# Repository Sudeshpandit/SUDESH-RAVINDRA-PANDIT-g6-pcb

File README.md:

# USB-TO-EtherCAT-Adapter-Board

A compact USB-to-EtherCAT adapter board that allows a USB host system to communicate with an EtherCAT network. An STM32 microcontroller handles the USB side and exchanges data with a LAN9252 EtherCAT slave controller, which manages the fieldbus protocol and drives two RJ45 ports for daisy-chain operation. The board is bus-powered from USB and designed in KiCad for industrial automation, embedded systems, and real-time networking use.

---

## Key Goals

**1. Reliable protocol bridging**
Provide a stable conversion path between USB and EtherCAT so a standard host machine can participate in a deterministic industrial network without dedicated fieldbus hardware.

**2. Standards-compliant hardware design**
Follow proper high-speed design practice — controlled differential routing, correct termination, clean power distribution, and stable clocking — so the board meets EtherCAT physical-layer requirements and operates reliably in noisy environments.

**3. Compact and practical integration**
Keep the board bus-powered, self-contained, and small enough to sit inline in an existing network, with edge-mounted connectors, mounting holes, and a debug header for easy deployment and development.

---

## Features

**Communication**
Full signal chain from USB host through the microcontroller to the EtherCAT slave controller, with two RJ45 ports allowing the adapter to be placed anywhere in a daisy-chained network.

**Design quality**
Length-matched differential pairs, proper termination networks, dedicated filtered supply rails, per-pin decoupling, and independent clock sources for the controller and the EtherCAT device.

**Usability**
Single-cable USB power, on-board 3.3 V regulation, status LEDs, reset switch, SWD programming header, and mounting holes for enclosure fitting.

---

## Hardware

| Item | Detail |
|---|---|
| Microcontroller | STM32F411CEUx (ARM Cortex-M4) |
| EtherCAT slave controller | Microchip LAN9252 |
| Configuration memory | 24LC512 I²C EEPROM |
| Network ports | 2x RJ45 (IN / OUT, integrated magnetics) |
| Host interface | USB |
| Power | USB bus powered, AMS1117-3.3 regulator |
| Debug | 4-pin SWD header |
| Design software | KiCad |

---

## Software and Tools Used

| Tool | Purpose |
|---|---|
| **KiCad** | Schematic capture, PCB layout, DRC/ERC |
| **KiCad Symbol & Footprint Editor** | Custom symbols and footprints |
| **KiCad 3D Viewer** | Mechanical and visual verification |
| **Gerber Viewer** | Fabrication output verification |

---

## Outputs / Deliverables

- Schematic (KiCad + PDF export)
- PCB layout (KiCad + PDF export)
- Gerber files (fabrication-ready)
- Drill files
- Bill of Materials (BOM)
- Pick and place file
- 3D render

---

## Applications

- Industrial automation and motion control
- EtherCAT slave/master development and testing
- Embedded systems requiring fieldbus connectivity
- Real-time networking and data acquisition setups

## Author

**Sudesh Pandit**
*(https://www.linkedin.com/in/sudeshpandits/)*

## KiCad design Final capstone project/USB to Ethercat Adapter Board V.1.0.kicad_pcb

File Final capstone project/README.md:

<div align="center" style="border: 2px solid #ccc; padding: 20px; border-radius: 12px; width: 80%; margin: auto; box-shadow: 0 0 10px rgba(0,0,0,0.15);">

  <h1 align="center" style="font-family: Arial; font-weight: 600; margin-top: 15px;">SURE ProEd (formerly SURE Trust) 
      </h1>
<h2 style="color: #2b6cb0; font-family: Arial;">Skill Upgradation for Rural youth Empowerment Trust</h2>
</div>

<hr style="border: 0; border-top: 1px solid #ccc; width: 80%;" />

<div style="padding: 20px; border: 2px solid #ddd; border-radius: 12px; width: 90%; margin: auto; background: #fafafa; font-family: Arial;">

<h2 style = "color:#333;"> Student Details </h2>
<div align = "left" style ="margin: 20px; font-size: 16px;">
    <p><strong>Name:</strong> Sudesh Ravindra Pandit </p>
    <p><strong>Email ID:</strong> sudeshpanditg6pcb@gmail.com </p>
    <p><strong>College Name:</strong> Dhole Patil College Of Engineering ,Pune  </p>
    <p><strong>Branch/Specialization :</strong> Electronics and Telecommunication Engineering </p>
    <p><strong>College ID:</strong> EN22170156 </p>
</div>

<hr style="border: 0; border-top: 1px solid #ccc; width: 80%;" />

<h2 style="color:#333;"> Course Details </h2>
<div align="left" style="margin: 20px; font-size: 16px;">
    <p><strong>Course Opted:</strong> PCB Designing </p>
    <p><strong>Instructor Name:</strong> Monika mam </p>
</div>
<div align="left" style="margin: 20px; font-size: 16px;">
    <p><strong>Duration:</strong> 6 Months </p>

<hr style="border: 0; border-top: 1px solid #ccc; width: 80%;" />

<h2 style="color:#333;"> Trainer Details </h2>
<div align="left" style="margin: 20px; font-size: 16px;">

<p><strong>Trainer Name:</strong> Paramesh Kumar </p>
<p><strong>Trainer Email ID:</strong> parameshkumar432@gmail.com </p>
<p><strong>Trainer Designation:</strong> Hardware Design Engineer </p>

<hr style="border: 0; border-top: 1px solid #ccc; width: 80%;" />

## **Table of Contents**
- [Course Learning](#course-learning-to-be-edited-by-student)
- [Projects Completed](#projects-completed)
- [Project Introduction](#project-introduction)
- [Technologies Used](#technologies-used)
- [Roles and Responsibilities](#roles-and-responsibilities)
- [Project Report](#project-report)
- [Learnings from LST & SST](#learnings-from-lst--sst)
- [Community Services](#community-services)
- [Certificate](#certificate)
- [Acknowledgments](#acknowledgments)

<hr style="border: 0; border-top: 1px solid #ccc; width: 80%;" />

## Overall Learning 

When I started, I barely knew how a PCB actually gets made — the first few days were confusing, and I kept hitting DRC errors without understanding why. Things started clicking as I worked through mistakes instead of just reading about them.

Over the internship I built up through 14 PCB projects, gaining hands-on experience with STM32 microcontrollers, SPI/I2C communication, and industrial protocols like EtherCAT — along the way strengthening my problem-solving (debugging DRC errors and routing conflicts), documentation, and the discipline of verifying a design before calling it done.

My final project, the USB to EtherCAT Adapter Board, brought a lot of that learning together — it needed me to combine what I'd picked up about power supply design, layout planning, and following proper design rules into one board.

Overall, this internship taught me that PCB design isn't something you understand by reading — you actually have to sit with the confusion for a while before it starts making sense.

<h2 style="color:#333;"> Projects Completed </h2>
<div align="left" style="margin: 20px; font-size: 16px;">

<p><strong><a href="#project1">Project 1:</a></strong> USB to EtherCAT Adapter Board V.1.0 </p>

<p><em></em></p>

</div>

<!-- Project 1 -->
<h3 id="project1">Project 1: USB to EtherCAT Adapter Board V.1.0 </h3>
<p>
 This project was completed as part of my internship at SURE Trust, where I designed and developed a 2-layer USB to EtherCAT Adapter Board (V1.0) using KiCad, applying core PCB design concepts taught during the training.
It focused on schematic design around an STM32F411 microcontroller and a LAN9252 EtherCAT slave controller, structured 2-layer routing with proper design-rule compliance, and implementing key features like USB communication, SPI/I2C interfacing, and dual RJ45 EtherCAT ports.
</p>
<p>
  <a href="https://github.com/sure-trust/SUDESH-RAVINDRA-PANDIT-g6-pcb/blob/492f94ba0c24407fa2a5996a74b2673d0c09e90f/Course%20report/SURE%20Trust%20Final%20Project%20%20Report.pdf" target="_blank"><strong>→ View Full Project Report</strong></a>
</p>

<hr style="height:1px; border-top:1px solid #ccc; width:80%;" />

## **References**

- [Wikipedia](https://wikipedia.com)
<!--you can add refrences over here in same syntax as above -->
---

## **Learnings from LST and SST**

<!-- add your experiences over here -->
Alongside the technical PCB work, we had daily Life Skill Training (LST) and Soft Skill Training (SST) sessions, where a different guest speaker was invited almost every day. What stood out to me was who these speakers actually were — professionals holding senior positions at well-known companies — sharing real experience rather than just theory from a textbook.

Honestly, some sessions connected with me more than others depending on the topic, but hearing people who've actually worked at that level talk about how they think, communicate, and handle real workplace situations gave me a different perspective than just focusing on the technical side of the internship. It made me realize that skills like communication, confidence, and how you present yourself matter just as much as technical ability when it comes to actually working in the industry.

## **Community Services**

<!-- add descreption in your own words -->

During my internship period, I participated in multiple community-oriented activities .....<!-- add descreption in your own words -->

### **Activities Involved**
  
 <!-- add the location where you have panted -->
- **Tree Plantation Drive** – Participated by planting trees and contributing to environmental improvement.

  <!-- add the location where you helped -->
- **Helping Elder Citizens** – Assisted two elderly individuals with simple daily tasks and provided support where needed. 

<!-- you can write impacts according to your experience in your words-->

### **Impact / Contribution**

<!-- add the location where you given -->
Tree Plantation Drive – Participated by planting trees and contributing to environmental improvement.
Helping Elder Citizens – Assisted two elderly individuals with simple daily tasks and provided support where needed.
These activities, alongside the core PCB design work, strengthened my sense of social responsibility and community engagement, reflecting SURE Trust's focus on holistic development beyond just technical skills.
### **Photos**

<!-- add your photos below -->
<!-- change url below with your image urls (inside  src='')-->

- These are just placeholder (sample) images <!-- remove this line -->

<div align="center">

</div>

---

## **Certificate**

The internship certificate serves as an official acknowledgment of the successful completion of my training period. It will be issued by the organization upon fulfilling all required tasks and meeting the performance expectations of the program. The certificate validates the skills, experience, and contributions made during the internship.

<!-- add your certificate image url below (inside src='')-->

---

## **Acknowledgments**

<!-- you can add Acknowledgments over here in same syntax as below . eg trainer name , company name , role etc -->

- [Prof. Radhakumari Challa](https://www.linkedin.com/in/prof-radhakumari-challa-a3850219b) , Executive Director and Founder - [SURE Trust](https://www.suretrustforruralyouth.com/)

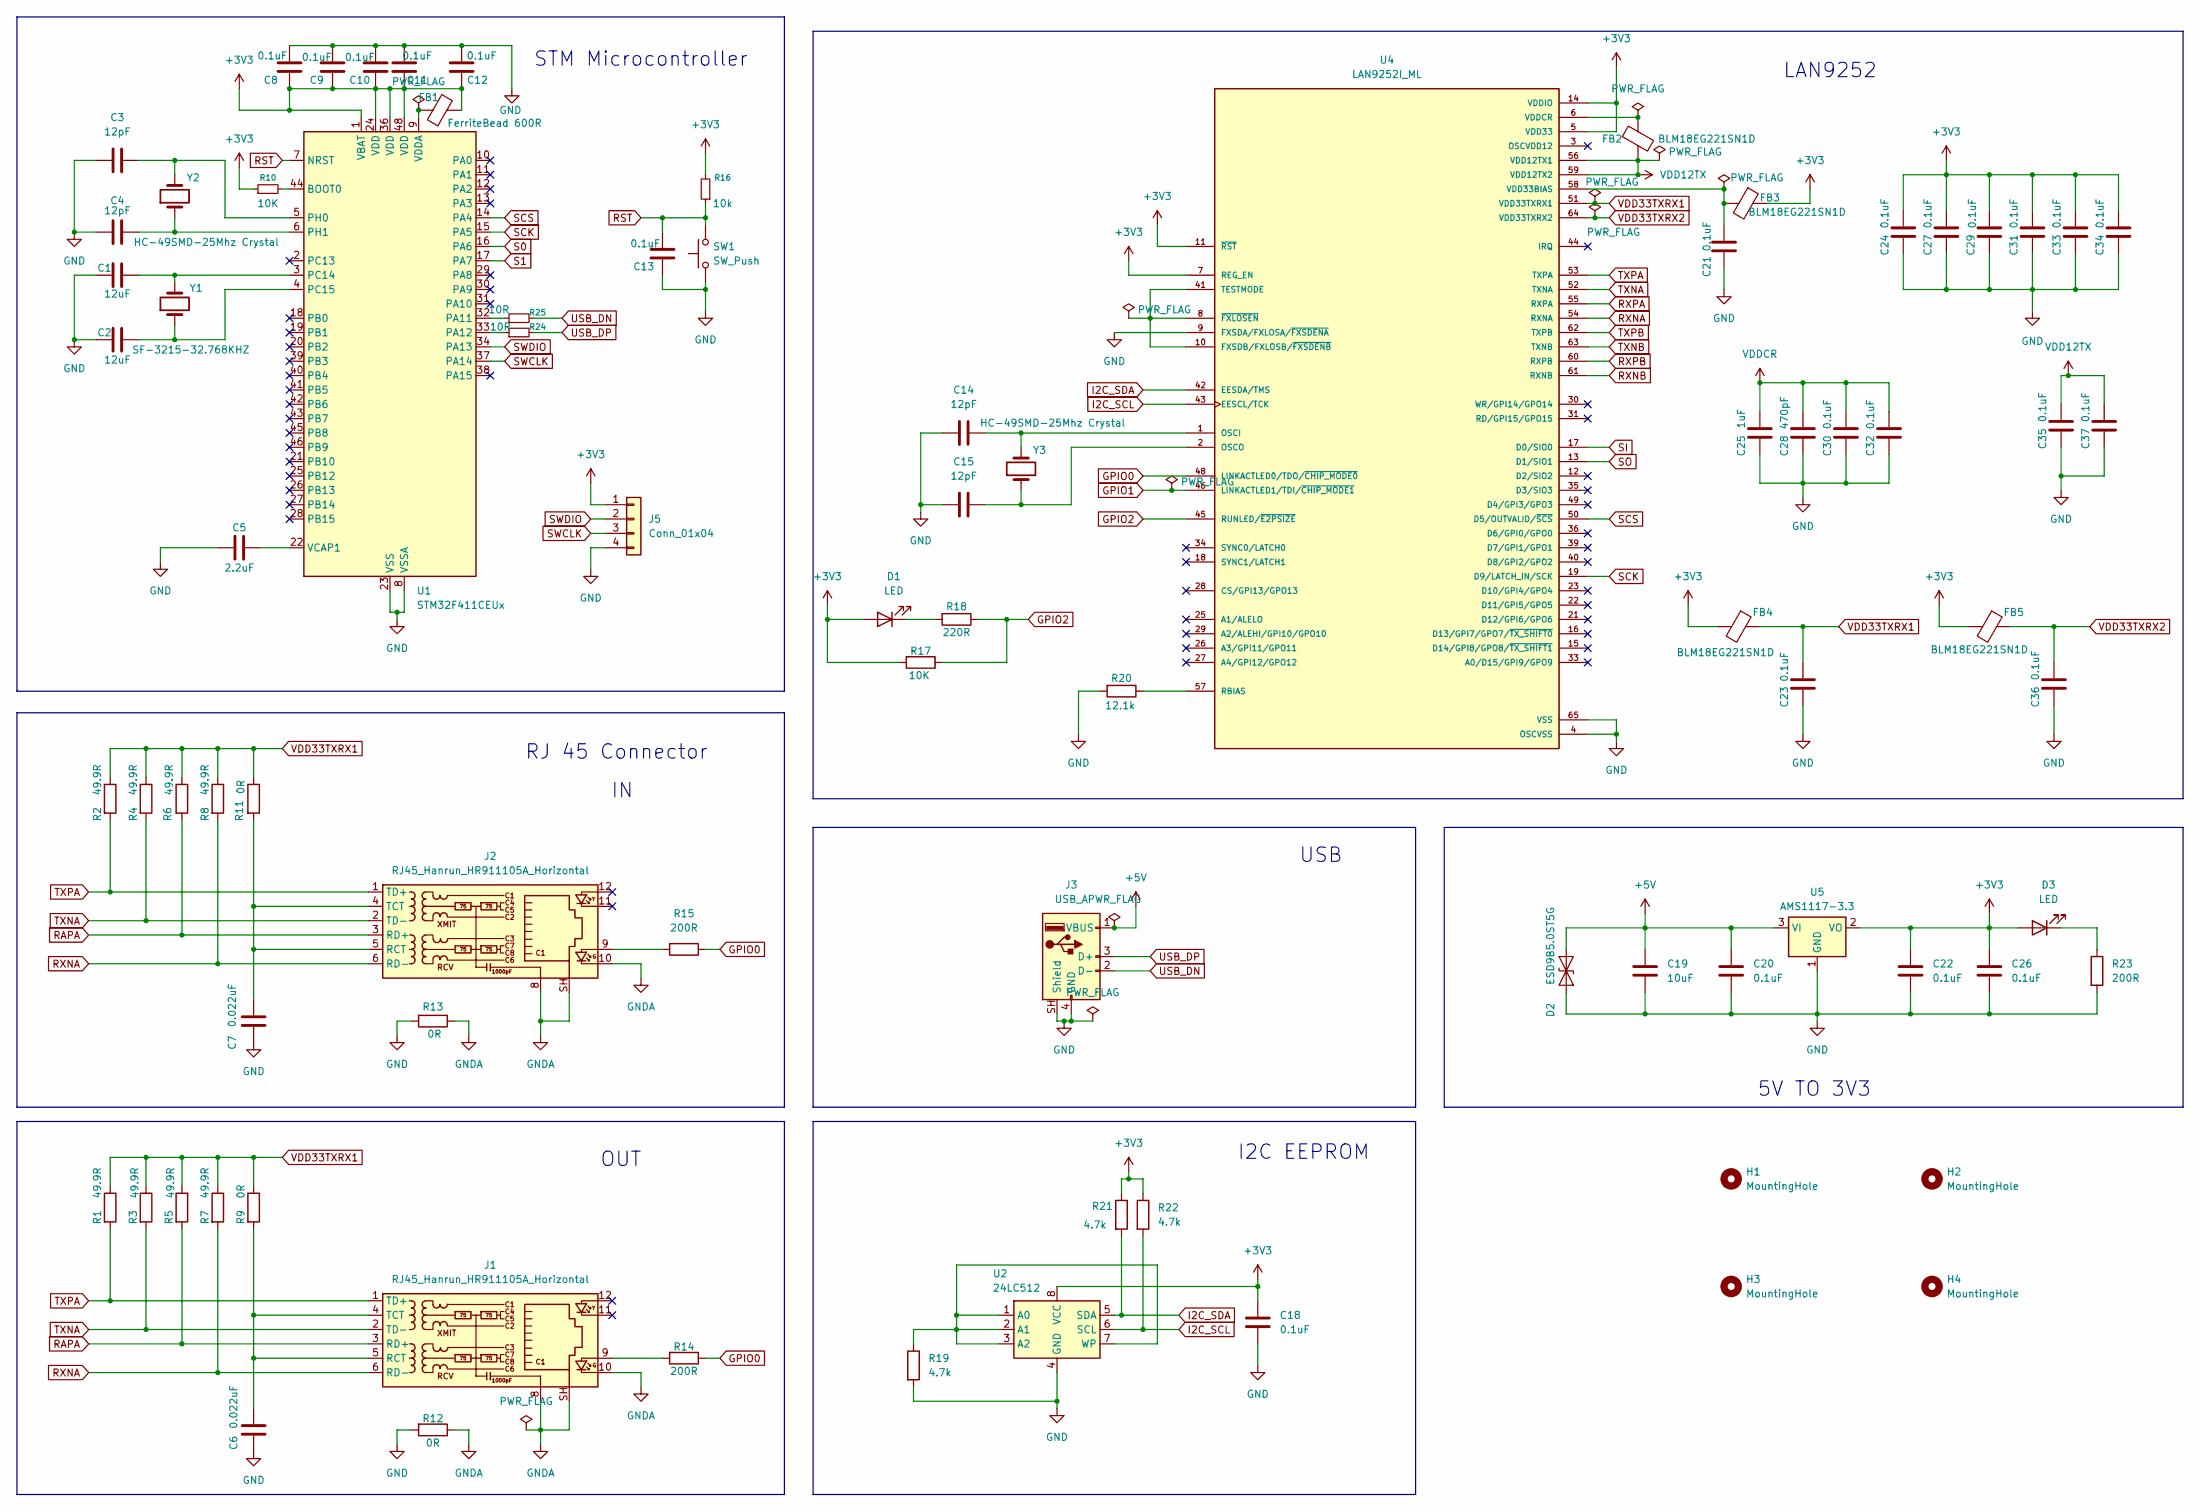
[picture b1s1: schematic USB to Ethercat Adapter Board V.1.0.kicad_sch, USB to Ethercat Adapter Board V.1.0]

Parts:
C1, C2: 12uF; C_0603_1608Metric
C3, C4, C14, C15: 12pF; C_0603_1608Metric
C5: 2.2uF; C_0805_2012Metric
C6, C7: 0.022uF; C_0603_1608Metric
C8, C9, C10, C11, C12, C13, C18, C20, C21, C22, C23, C24, C27, C29, C30, C31, C32, C33, C34, C35, C36, C37: 0.1uF; C_0603_1608Metric
C19: 10uF; C_0805_2012Metric
C25: 1uF; C_0603_1608Metric
C26: 0.1uF; C_0805_2012Metric
C28: 470pF; C_0603_1608Metric
D1, D3: LED; LED_0603_1608Metric
D2: ESD9B5.0ST5G; C_0805_2012Metric
FB1: FerriteBead 600R; L_0603_1608Metric
FB2, FB3, FB4, FB5: BLM18EG221SN1D; L_0603_1608Metric
H1, H2, H3, H4: MountingHole; MountingHole_3.2mm_M3
J1, J2: RJ45_Hanrun_HR911105A_Horizontal
J3: USB_A; USB_A_CNCTech_1001-011-01101_Horizontal
J5: Conn_01x04; PinHeader_1x04_P2.54mm_Vertical
R1, R2, R3, R4, R5, R6, R7, R8: 49.9R; R_0603_1608Metric
R9, R11, R12, R13: 0R; R_0603_1608Metric
R10, R17: 10K; R_0603_1608Metric
R14, R15, R23: 200R; R_0603_1608Metric
R16: 10k; R_0603_1608Metric
R18: 220R; R_0603_1608Metric
R19, R21, R22: 4.7k; R_0603_1608Metric
R20: 12.1k; R_0603_1608Metric
R24, R25: 10R; R_0603_1608Metric
SW1: SW_Push; SW_SPST_B3U-1000P
U1: STM32F411CEUx; QFN-48-1EP_7x7mm_P0.5mm_EP5.6x5.6mm
U2: 24LC512; TSSOP-8_3x3mm_P0.65mm
U4: LAN9252I_ML; QFN50P900X900X100-65N-; PARTREV DS00001909B
U5: AMS1117-3.3; SOT-223-3_TabPin2
Y1: SF-3215-32.768KHZ; Crystal_SMD_3215-2Pin_3.2x1.5mm
Y2, Y3: HC-49SMD-25Mhz Crystal; Crystal_SMD_HC49-SD

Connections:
+3V3: C8.1, C9.1, C10.1, C11.1, C12.1, C18.2, C22.2, C24.2, C26.2, C27.2, C29.2, C31.2, C33.2, C34.2, D1.2 (A), D3.2 (A), FB1.2, FB3.1, FB4.2, FB5.2, J5.1, R10.1, R16.2, R17.2, R21.1, R22.1, U1.1 (VBAT), U1.24 (VDD), U1.36 (VDD), U1.48 (VDD), U2.8 (VCC), U4.5 (VDD33), U4.7 (REG_EN), U4.11 (~RST), U4.14 (VDDIO), U4.20 (VDDIO), U4.32 (VDDIO), U4.37 (VDDIO), U4.47 (VDDIO), U5.2 (VO)
+5V: C19.2, C20.2, D2.2 (A2), J3.1 (VBUS), U5.3 (VI)
GND: C1.1, C2.1, C3.1, C4.1, C5.1, C6.2, C7.2, C8.2, C9.2, C10.2, C11.2, C12.2, C13.1, C14.1, C15.1, C18.1, C19.1, C20.1, C21.1, C22.1, C23.1, C24.1, C25.1, C26.1, C27.1, C28.1, C29.1, C30.1, C31.1, C32.1, C33.1, C34.1, C35.1, C36.1, C37.1, D2.1 (A1), J3.4 (GND), J3.SH (Shield), J5.4, R12.2, R13.2, R19.2, R20.2, R23.2, SW1.1, U1.8 (VSSA), U1.23 (VSS), U1.35 (VSS), U1.47 (VSS), U1.49 (VSS), U2.4 (GND), U4.4 (OSCVSS), U4.9 (FXSDA/FXLOSA/~FXSDENA), U4.65 (VSS), U5.1 (GND)
GNDA: J1.8, J1.10, J1.SH, J2.8, J2.10, J2.SH, R12.1, R13.1
GPIO0: R14.1, R15.1, U4.48 (LINKACTLED0/TDO/~CHIP_MODE0)
GPIO1: U4.46 (LINKACTLED1/TDI/~CHIP_MODE1)
GPIO2: R17.1, R18.1, U4.45 (RUNLED/~E2PSIZE)
I2C_SCL: R22.2, U2.6 (SCL), U4.43 (EESCL/TCK)
I2C_SDA: R21.2, U2.5 (SDA), U4.42 (EESDA/TMS)
unnamed: D1.1 (K), R18.2
unnamed: D3.1 (K), R23.1
unnamed: J1.9, R14.2
unnamed: C6.1, J1.4 (TCT), J1.5 (RCT), R9.2
unnamed: J2.9, R15.2
unnamed: C7.1, J2.4 (TCT), J2.5 (RCT), R11.2
unnamed: R10.2, U1.44 (BOOT0)
unnamed: R25.1, U1.32 (PA11)
unnamed: R24.1, U1.33 (PA12)
unnamed: C1.2, U1.3 (PC14), Y1.2
unnamed: C2.2, U1.4 (PC15), Y1.1
unnamed: C3.2, U1.5 (PH0), Y2.2
unnamed: C4.2, U1.6 (PH1), Y2.1
unnamed: C5.2, U1.22 (VCAP1)
unnamed: FB1.1, U1.9 (VDDA)
unnamed: R19.1, U2.1 (A0), U2.2 (A1), U2.3 (A2), U2.7 (WP)
unnamed: U4.8 (~FXLOSEN), U4.10 (FXSDB/FXLOSB/~FXSDENB), U4.41 (TESTMODE)
unnamed: C14.2, U4.1 (OSCI), Y3.2
unnamed: C15.2, U4.2 (OSCO), Y3.1
unnamed: R20.1, U4.57 (RBIAS)
unnamed: C21.2, FB3.2, U4.58 (VDD33BIAS)
RAPA: J1.3 (RD+), J2.3 (RD+), R5.2, R6.2
RST: C13.2, R16.1, SW1.2, U1.7 (NRST)
RXNA: J1.6 (RD-), J2.6 (RD-), R7.2, R8.2, U4.54 (RXNA)
RXNB: U4.61 (RXNB)
RXPA: U4.55 (RXPA)
RXPB: U4.60 (RXPB)
S0: U1.16 (PA6)
S1: U1.17 (PA7)
SCK: U1.15 (PA5), U4.19 (D9/LATCH_IN/SCK)
SCS: U1.14 (PA4), U4.50 (D5/OUTVALID/~SCS)
SI: U4.17 (D0/SIO0)
SO: U4.13 (D1/SIO1)
SWCLK: J5.3, U1.37 (PA14)
SWDIO: J5.2, U1.34 (PA13)
TXNA: J1.2 (TD-), J2.2 (TD-), R3.2, R4.2, U4.52 (TXNA)
TXNB: U4.63 (TXNB)
TXPA: J1.1 (TD+), J2.1 (TD+), R1.2, R2.2, U4.53 (TXPA)
TXPB: U4.62 (TXPB)
USB_DN: J3.2 (D-), R25.2
USB_DP: J3.3 (D+), R24.2
VDD12TX: C35.2, C37.2, FB2.2, U4.56 (VDD12TX1), U4.59 (VDD12TX2)
VDD33TXRX1: C23.2, FB4.1, R1.1, R2.1, R3.1, R4.1, R5.1, R6.1, R7.1, R8.1, R9.1, R11.1, U4.51 (VDD33TXRX1)
VDD33TXRX2: C36.2, FB5.1, U4.64 (VDD33TXRX2)

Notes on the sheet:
RJ 45 Connector
I2C EEPROM
LAN9252
OUT
5V TO 3V3
USB
STM Microcontroller

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
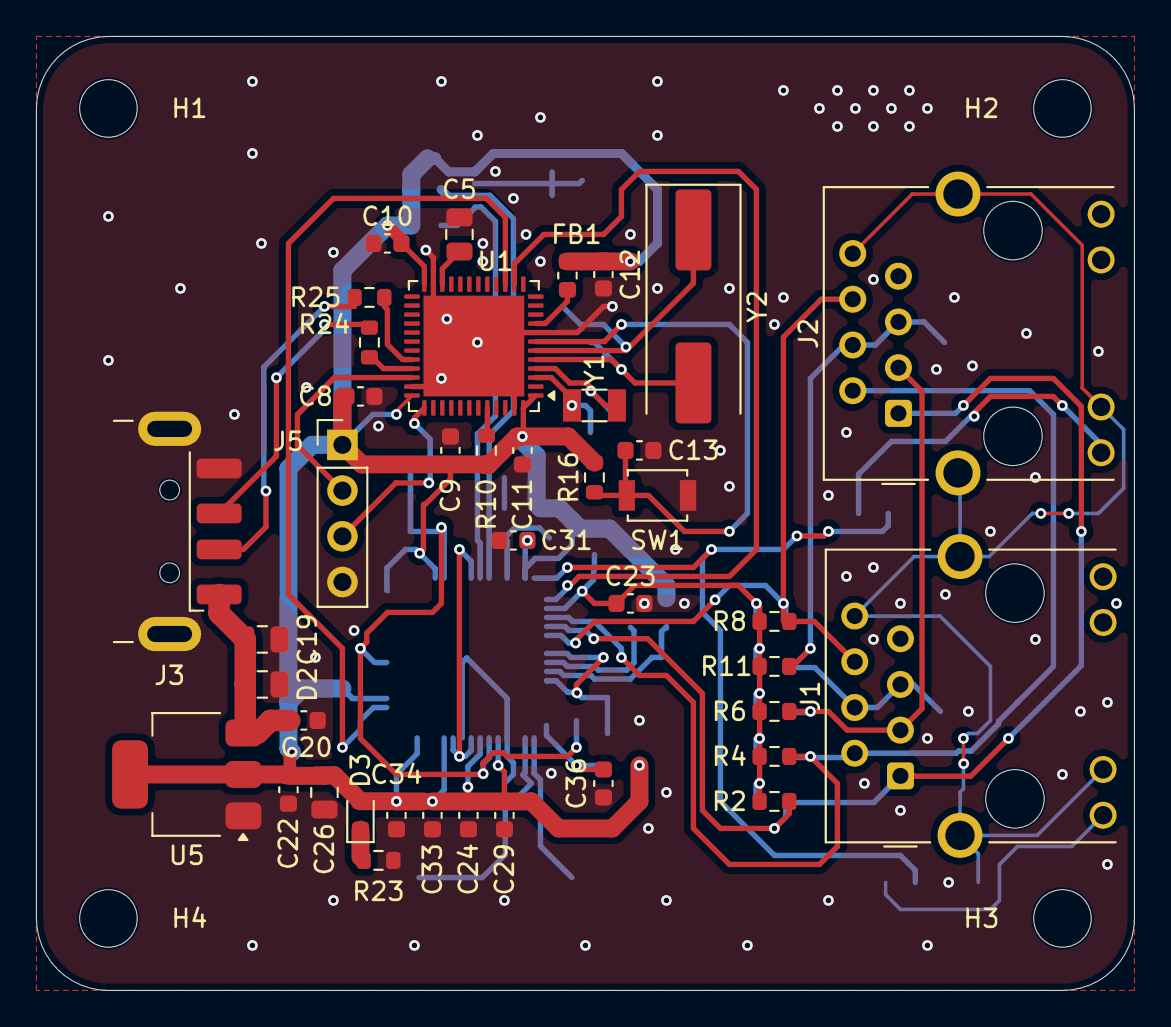
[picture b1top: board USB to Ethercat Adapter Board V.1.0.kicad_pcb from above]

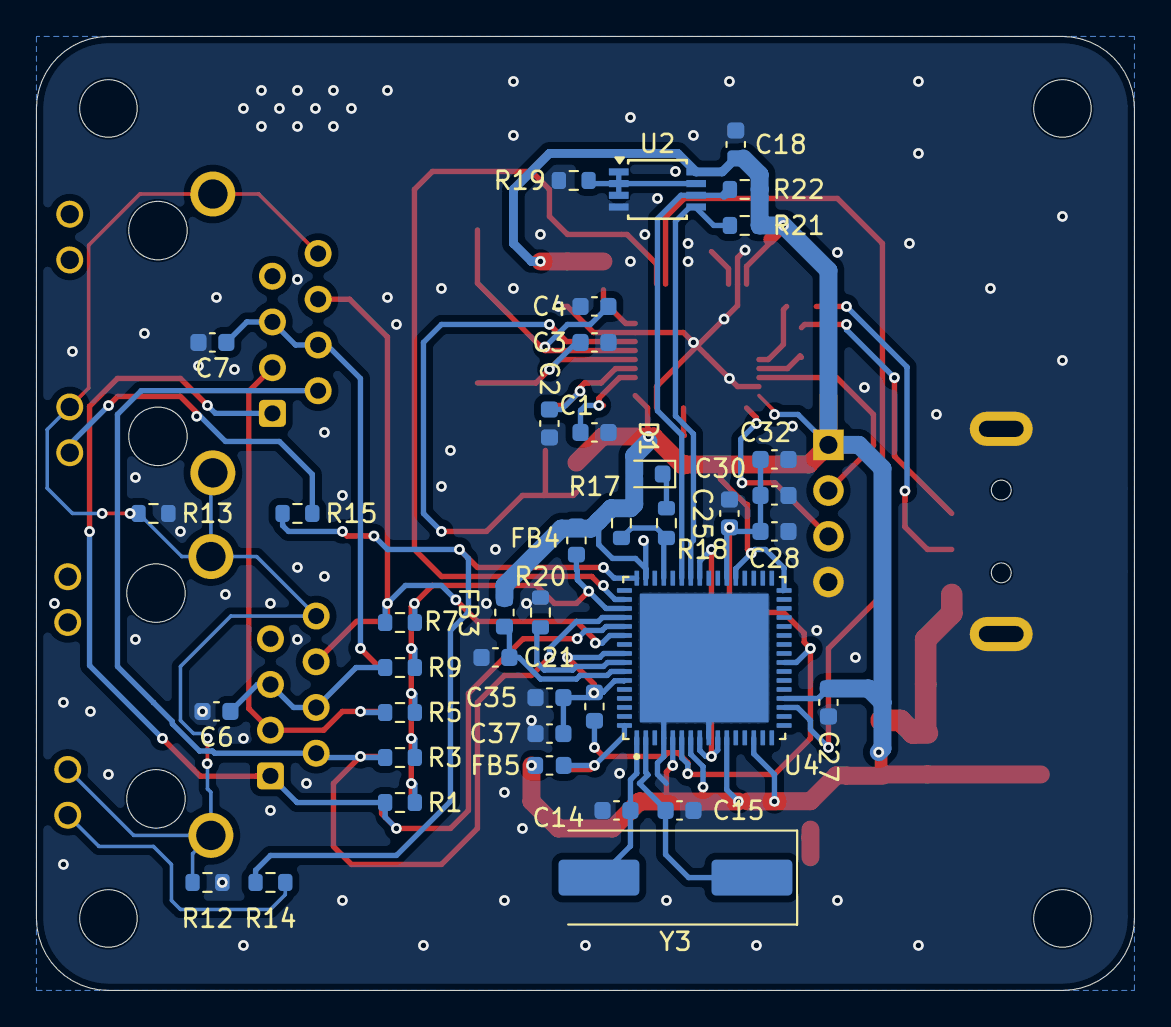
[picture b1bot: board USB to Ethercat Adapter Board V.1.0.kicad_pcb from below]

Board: 2 copper layers, 61.0 x 53.0 mm, 84 parts (40 on the bottom side), 44 nets.

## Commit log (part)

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2026-04-11 Added folder
